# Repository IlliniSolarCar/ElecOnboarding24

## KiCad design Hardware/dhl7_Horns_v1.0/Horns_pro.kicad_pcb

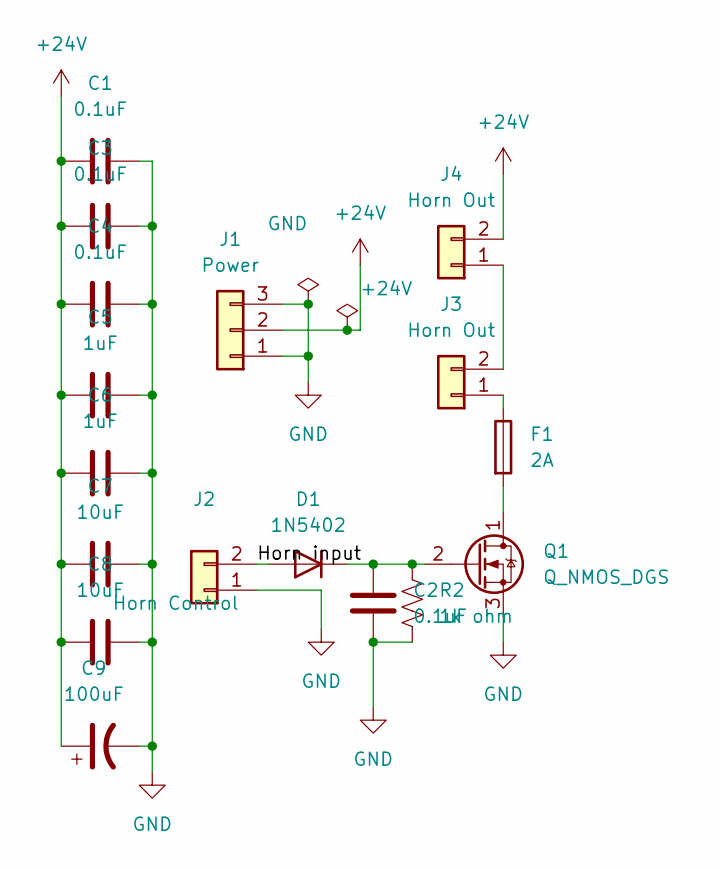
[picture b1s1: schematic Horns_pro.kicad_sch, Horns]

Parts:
C1, C2, C3, C4: 0.1uF; C_0603_1608Metric_Pad1.08x0.95mm_HandSolder; MPN 0201W104K100LE
C5, C6: 1uF; C_0603_1608Metric_Pad1.08x0.95mm_HandSolder; MPN JMK105BJ105KV-F
C7, C8: 10uF; C_0603_1608Metric_Pad1.08x0.95mm_HandSolder; MPN CL05A106MP5NUNC
C9: 100uF; C_0603_1608Metric_Pad1.08x0.95mm_HandSolder; MPN 865080340001
D1: 1N5402; D_DO-201AD_P15.24mm_Horizontal; MPN ES2DA-13-F
F1: 2A; Fuse_1206_3216Metric; MPN ERB-RD2R00X
J1: Power; Molex_KK-254_AE-6410-03A_1x03_P2.54mm_Vertical; MPN 0022232031
J2: Horn Control; Molex_KK-254_AE-6410-02A_1x02_P2.54mm_Vertical; MPN 0022232021
J3, J4: Horn Out; Molex_KK-254_AE-6410-02A_1x02_P2.54mm_Vertical; MPN 0022232021
Q1: Q_NMOS_DGS; TO-252-2; MPN IRFR010PBF
R2: 1k ohm; R_0603_1608Metric_Pad0.98x0.95mm_HandSolder

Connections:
+24V: C1.1, C3.1, C4.1, C5.1, C6.1, C7.1, C8.1, C9.1, J1.2, J4.2
/Horn input: D1.2 (A), J2.2
GND: C1.2, C2.1, C3.2, C4.2, C5.2, C6.2, C7.2, C8.2, C9.2, J1.1, J1.3, J2.1, Q1.3 (S), R2.1
unnamed: C2.2, D1.1 (K), Q1.2 (G), R2.2
unnamed: F1.1, J3.1
unnamed: J3.2, J4.1
unnamed: F1.2, Q1.1 (D)

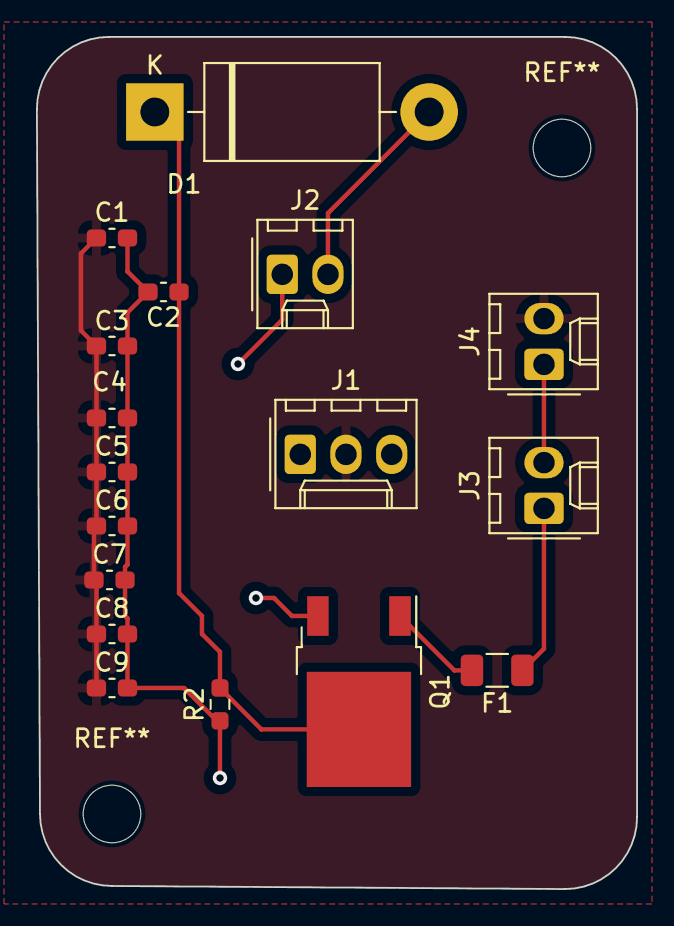
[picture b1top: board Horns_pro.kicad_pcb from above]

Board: 2 copper layers, 33.3 x 47.3 mm, 17 parts (0 on the bottom side), 7 nets.

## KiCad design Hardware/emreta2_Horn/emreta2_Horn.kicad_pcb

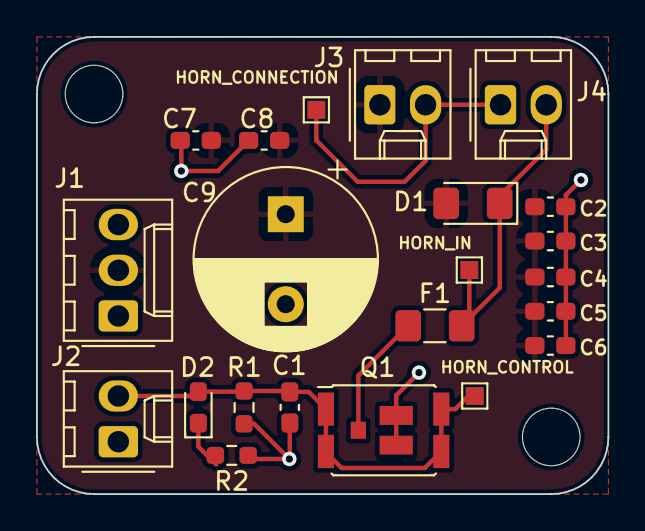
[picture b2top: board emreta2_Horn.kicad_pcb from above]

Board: 2 copper layers, 31.7 x 25.4 mm, 22 parts (0 on the bottom side), 7 nets.

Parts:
C1, C2, C3, C4: 0.1uF; C_0603_1608Metric_Pad1.08x0.95mm_HandSolder
C5, C6: 1uF; C_0603_1608Metric_Pad1.08x0.95mm_HandSolder
C7, C8: 10uF; C_0603_1608Metric_Pad1.08x0.95mm_HandSolder
C9: 100uF; CP_Radial_D10.0mm_P5.00mm
D1: ES2DA-13-F; D_1206_3216Metric_Pad1.42x1.75mm_HandSolder
D2: LED; LED_0603_1608Metric_Pad1.05x0.95mm_HandSolder
F1: 2A Fuse; Fuse_1206_3216Metric_Pad1.42x1.75mm_HandSolder
HORN_CONNECTION: TestPoint_Pad_1.0x1.0mm
HORN_CONTROL: TestPoint_Pad_1.0x1.0mm
HORN_IN: TestPoint_Pad_1.0x1.0mm
J1: Conn_01x03; Molex_KK-254_AE-6410-03A_1x03_P2.54mm_Vertical
J2, J3, J4: Conn_01x02; Molex_KK-254_AE-6410-02A_1x02_P2.54mm_Vertical
Q1: IRFR010PBF; DirectFET_MT
R1, R2: 1K; R_0603_1608Metric_Pad0.98x0.95mm_HandSolder

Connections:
+24V: C2.2, C3.2, C4.2, C5.2, C6.2, C7.2, C8.2, C9.1, D1.2 (A), J1.2, J3.1
/HORN_CONTROL: C1.2, D2.2 (A), HORN_CONTROL.1, J2.2, Q1.1 (G), R1.2
/HORN_IN: D1.1 (K), F1.2, HORN_IN.1, J4.2
GND: C1.1, C2.1, C3.1, C4.1, C5.1, C6.1, C7.1, C8.1, C9.2, J1.1, J1.3, J2.1, Q1.3 (S), R1.1, R2.1
unnamed: D2.1 (K), R2.2
unnamed: HORN_CONNECTION.1, J3.2, J4.1
unnamed: F1.1, Q1.2 (D)

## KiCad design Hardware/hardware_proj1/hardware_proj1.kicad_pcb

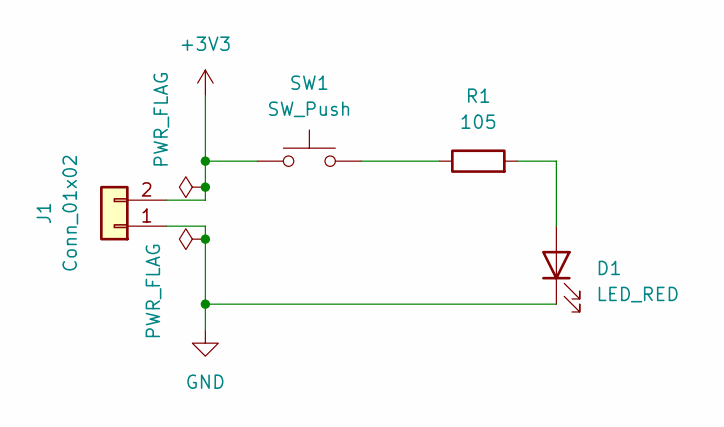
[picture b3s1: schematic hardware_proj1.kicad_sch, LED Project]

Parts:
D1: LED_RED; LED_0603_Symbol_on_F.SilkS
J1: Conn_01x02; Molex_KK-254_AE-6410-02A_1x02_P2.54mm_Vertical; MPN 022272021
R1: 105; R_0603_1608Metric_Pad0.98x0.95mm_HandSolder
SW1: SW_Push; SW_DIP_SPSTx01_Slide_6.7x4.1mm_W8.61mm_P2.54mm_LowProfile; MPN 1825910-6

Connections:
+3V3: J1.2, SW1.1
GND: D1.1 (K), J1.1
unnamed: D1.2 (A), R1.2
unnamed: R1.1, SW1.2

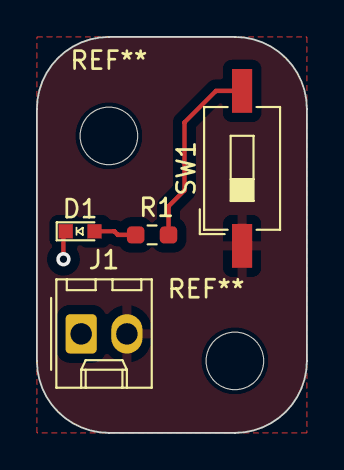
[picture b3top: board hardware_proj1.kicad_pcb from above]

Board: 2 copper layers, 15.0 x 22.0 mm, 4 parts (0 on the bottom side), 4 nets.

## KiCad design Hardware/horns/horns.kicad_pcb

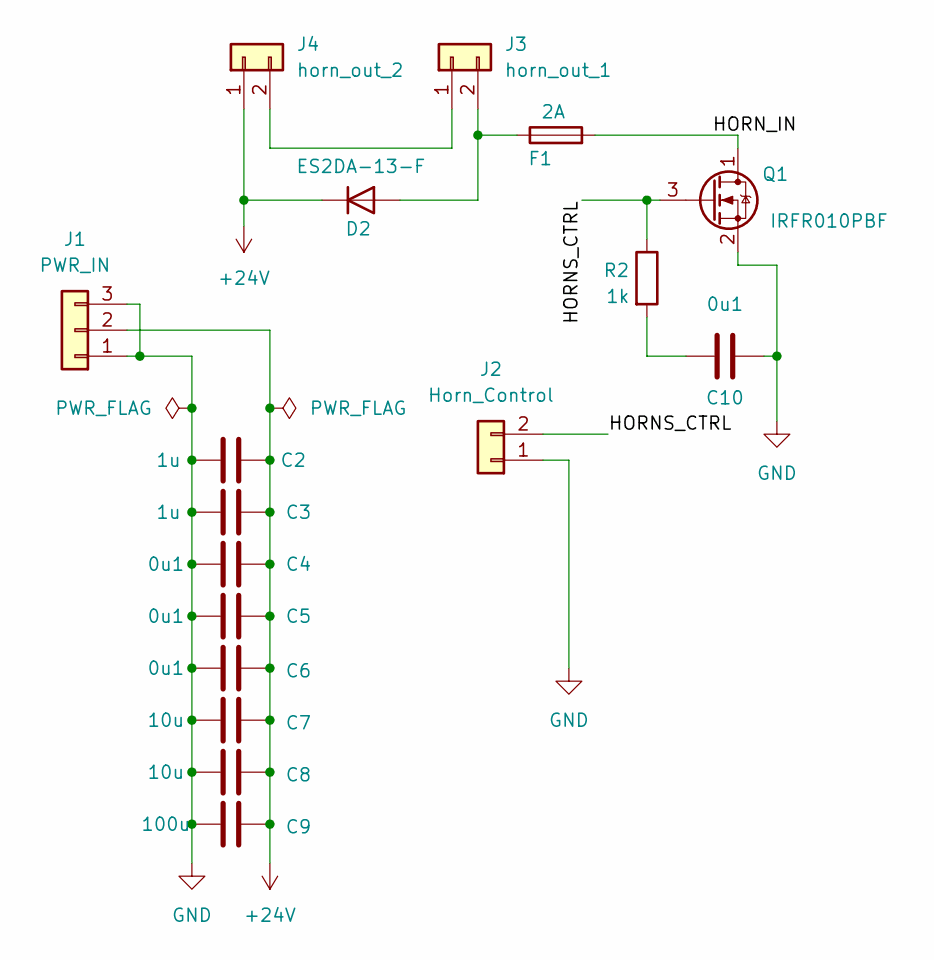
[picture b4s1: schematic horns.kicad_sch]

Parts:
C2, C3: 1u; C_0805_2012Metric
C4, C5, C6, C10: 0u1; C_0805_2012Metric
C7, C8: 10u; C_0805_2012Metric
C9: 100u; CP_Oval_L16.0mm_W8.0mm_P11.5mm
D2: ES2DA-13-F; D_SMA
F1: 2A; Fuse_Littelfuse_1206
J1: PWR_IN; Molex_Micro-Fit_3.0_43650-0300_1x03_P3.00mm_Horizontal
J2: Horn_Control; Molex_Micro-Fit_3.0_43650-0200_1x02_P3.00mm_Horizontal
J3: horn_out_1; Molex_Micro-Fit_3.0_43650-0200_1x02_P3.00mm_Horizontal
J4: horn_out_2; Molex_Micro-Fit_3.0_43650-0200_1x02_P3.00mm_Horizontal
Q1: IRFR010PBF; TO-252-2
R2: 1k; R_0603_1608Metric_Pad0.98x0.95mm_HandSolder

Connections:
+24V: C2.2, C3.2, C4.2, C5.2, C6.2, C7.2, C8.2, C9.2, D2.1 (K), J1.2, J4.1; also elsewhere on the board
/HORNS_CTRL: J2.2, Q1.3 (G), R2.1
/HORN_IN: F1.2, Q1.1 (D)
GND: C2.1, C3.1, C4.1, C5.1, C6.1, C7.1, C8.1, C9.1, C10.1, J1.1, J1.3, J2.1, Q1.2 (S); also elsewhere on the board
unnamed: C10.2, R2.2
unnamed: D2.2 (A), F1.1, J3.2
unnamed: J3.1, J4.2

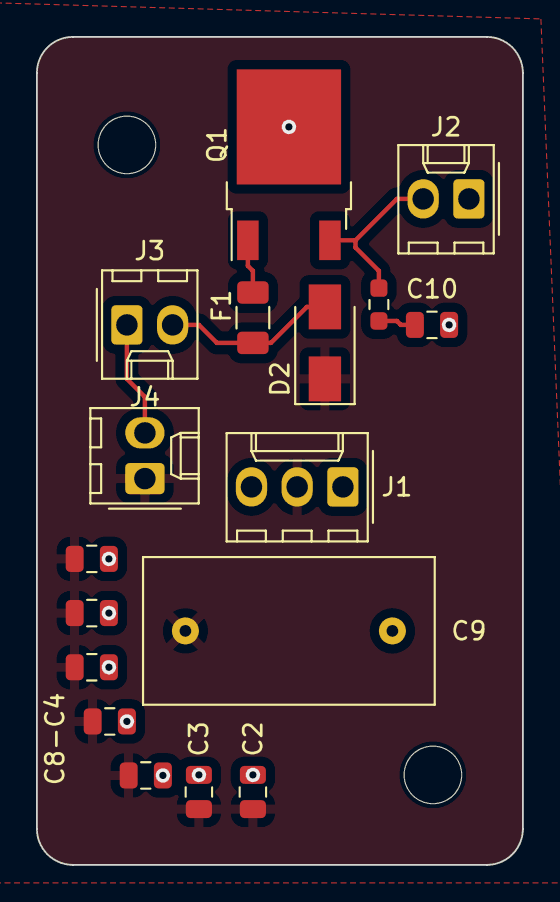
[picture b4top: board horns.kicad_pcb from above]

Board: 2 copper layers, 27.0 x 46.0 mm, 17 parts (0 on the bottom side), 7 nets.

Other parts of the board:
C8-C4: 10u; C_0805_2012Metric

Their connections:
+24V: C8-C4.2; also elsewhere on the board
GND: C8-C4.1; also elsewhere on the board

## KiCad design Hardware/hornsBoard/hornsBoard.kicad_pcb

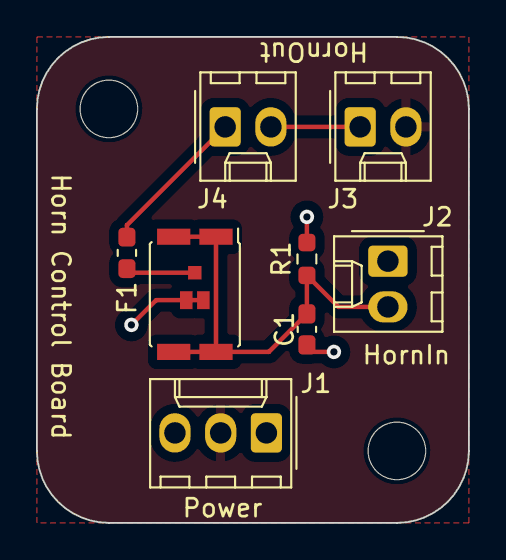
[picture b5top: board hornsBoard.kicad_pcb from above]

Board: 2 copper layers, 24.0 x 27.0 mm, 8 parts (0 on the bottom side), 6 nets.

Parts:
C1: C; C_0603_1608Metric_Pad1.08x0.95mm_HandSolder
F1: 2A; Fuse_0603_1608Metric_Pad1.05x0.95mm_HandSolder
J1: Conn_01x03; Molex_KK-254_AE-6410-03A_1x03_P2.54mm_Vertical
J2, J3, J4: Conn_01x02; Molex_KK-254_AE-6410-02A_1x02_P2.54mm_Vertical
Q2: IRF6785; DirectFET_MZ
R1: R_US; R_0603_1608Metric_Pad0.98x0.95mm_HandSolder

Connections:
/24V: J1.2, J3.2
/Horn_Signal: C1.1, J2.2, Q2.1 (D), R1.1
GND: C1.2, J1.1, J1.3, J2.1, Q2.3 (S), R1.2
unnamed: J3.1, J4.2
unnamed: F1.1, J4.1
unnamed: F1.2, Q2.2 (G)

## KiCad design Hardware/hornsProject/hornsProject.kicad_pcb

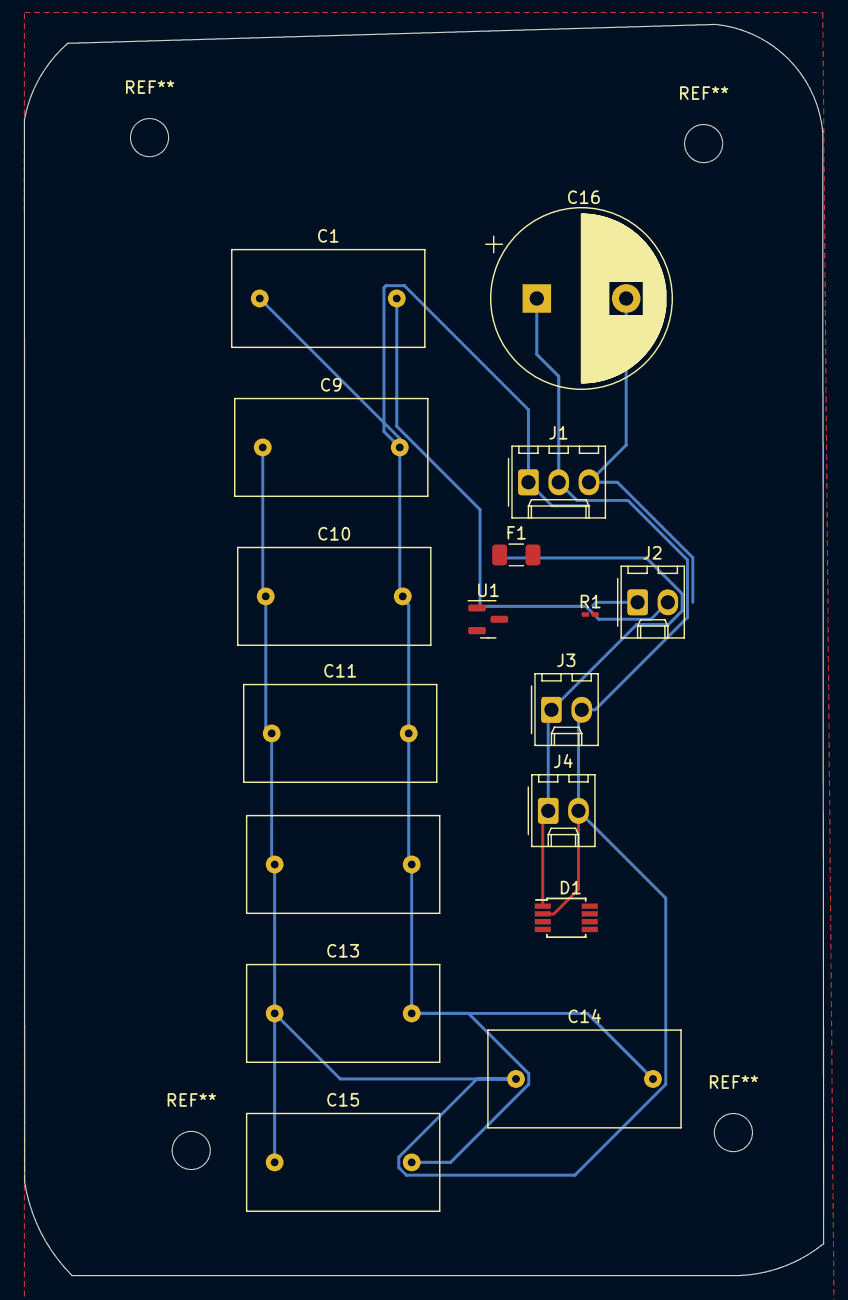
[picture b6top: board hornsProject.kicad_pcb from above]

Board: 2 copper layers, 67.1 x 105.0 mm, 17 parts (0 on the bottom side), 4 nets.

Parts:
C1, C9, C10, C11: 0.1uF; CP_Oval_L16.0mm_W8.0mm_P11.5mm
C12, C13: 1uF; CP_Oval_L16.0mm_W8.0mm_P11.5mm
C14, C15: 10uF; CP_Oval_L16.0mm_W8.0mm_P11.5mm
C16: 100uF; CP_Radial_D14.5mm_P7.50mm
D1: RECTIFIER DIODE; Diodes_MSOP-8
F1: 2A; Fuse_1206_3216Metric
J1: Conn_01x03; Molex_KK-254_AE-6410-03A_1x03_P2.54mm_Vertical
J2, J3, J4: Conn_01x02; Molex_KK-254_AE-6410-02A_1x02_P2.54mm_Vertical
R1: 1k ohm; R_0201_0603Metric_Pad0.64x0.40mm_HandSolder
U1: MOSFET; SOT-23

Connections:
+24V: C9.1, C10.1, C11.1, C12.1, C13.1, C14.1, C15.1, C16.1, D1.2 (A), J1.2, J3.2, J4.2
/HORN_CTRL: C1.2, J2.2, R1.2, U1.1 (Gate)
/HORN_IN: D1.1 (K), F1.1, J3.1, J4.1
GND: C1.1, C9.2, C10.2, C11.2, C12.2, C13.2, C14.2, C15.2, C16.2, J1.1, J1.3, J2.1, R1.1
